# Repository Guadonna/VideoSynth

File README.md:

# VideoSynth

**R1: схемы и две разведённые PCB KiCad 9, визуальный эмулятор и результаты проверок.** Один монохромный выход 480i, шесть осцилляторов, экранная матрица до 36 связей, два CV DC…100 Гц, Eurorack 42 HP, модуль ESP32-P4.

- [Начать с обзора R1](docs/r1/README.md)
- [Скачать автономный эмулятор HTML](https://raw.githubusercontent.com/Guadonna/VideoSynth/main/dist/VideoSynth-R1.html) — сохраните файл и откройте в браузере
- [Основная схема PDF](hardware/kicad/core/core-schematic.pdf) / [схема панели PDF](hardware/kicad/panel/panel-schematic.pdf)
- [Проекты KiCad и PCB](hardware/kicad/) / [полный архив R1](dist/VideoSynth-R1-prototype.zip)
- [Проверки и ограничения](docs/r1/validation.md)
- [BOM](hardware/bom-r1.csv) / [смета](hardware/cost-estimate-usd.csv) / [испытания прототипа](docs/r1/bringup.md)

## Запуск приложения

Нужен Node.js 20+. Готовый WASM включён в репозиторий; для самого приложения установка пакетов не нужна.

```sh
npm start
```

Сервер слушает порт 4173; приложение находится по пути `/app/index.html`. В облачной среде используйте предпросмотр порта 4173. Можно также открыть скачанный `dist/VideoSynth-R1.html` без сервера: код, изображения плат и WASM встроены в файл.

**Эмулятор 0.6.2:** микс перемножает выбранные биполярные OSC; AM работает как кольцевая модуляция со сменой полярности. Для сравнения добавлены сцены «Перемножение» и «AM · инверсия». Скачайте обновлённый HTML вместо старого файла; версия указана внизу страницы. [Формулы и поведение обратной связи](docs/r1/dsp.md), [изменения и проверки](docs/r1/modulation-fixes.md).

Исправление пустого экрана из 0.6.1 сохранено: при отказе Worker автоматически включается совместимый режим с тем же WASM. [Подробности запуска](docs/r1/emulator-fixes.md).

Для тестов нужны C-компилятор и зависимости разработки:

```sh
npm ci
npm test
npm run test:browser
npm run test:spice
```

Браузерный тест запускается при работающем сервере; ему нужен Chromium (`CHROMIUM=/путь/к/chromium`). SPICE использует `libngspice`. [Полное воспроизведение сборки и CAD-проверок](docs/r1/validation.md).

R1 — инженерный прототип. Нулевые ERC/DRC и программная эмуляция не подтверждают реальный видеосигнал, устойчивость CV и скорость ESP32-P4. Готовой прошивки платы пока нет. Изготовление не заказывалось.

## История исследования

Документы прежних этапов сохранены без изменения исторических выводов:

- [ТЗ v0.4](docs/requirements/video_synth_TZ_v0.4.md), [исследование v0.4](docs/feasibility-v0.4.md)
- [ТЗ v0.5](docs/requirements/video_synth_TZ_v0.5.md), [исследование v0.5](docs/feasibility-v0.5.md), [выжимка](docs/summary-v0.5.md)

Новый запрос пользователя разрешил схему и PCB, готовый модуль ESP32-P4 и 42 HP. Численные правила модуляции R1 описаны отдельно как инженерные допущения, а не как ранее согласованные требования.

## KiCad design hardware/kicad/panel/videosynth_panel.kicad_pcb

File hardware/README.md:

# VideoSynth R1 hardware

Open `kicad/core/videosynth_core.kicad_pro` and `kicad/panel/videosynth_panel.kicad_pro` in KiCad 9. Both projects include editable schematics, routed four-layer PCBs and local symbol libraries. PDFs are `core-schematic.pdf` and `panel-schematic.pdf` in the respective folders. The two boards use separate reference-designator namespaces.

`design.json` / `tools/design.py` describe electrical connectivity and initial placement. `bom-r1.csv` lists physical parts; blank MPNs and candidates still require procurement qualification. `external-assemblies.csv` includes module, display and harnesses beyond the PCB BOM. Front-panel drawing in `panel/` is provisional.

Verification: `bash scripts/verify-hardware.sh` from the repository root. It exports schematics/netlists, runs ERC/DRC, compares all PCB pads to the manifest and runs linear CV SPICE. It does not regenerate the PCB.

**Do not run `tools/build_kicad.py` without `--schematics-only` on the finished layout: full regeneration intentionally replaces routed boards.** Router helper scripts are development tools, not a production automation pipeline.

R1 is a testable prototype design, not a manufacturing release. Mandatory module FET2 removal, power harness wiring, unqualified component substitutions, analog/timing risks and mechanical gaps are documented in [hardware.md](../docs/r1/hardware.md). No production order has been placed.

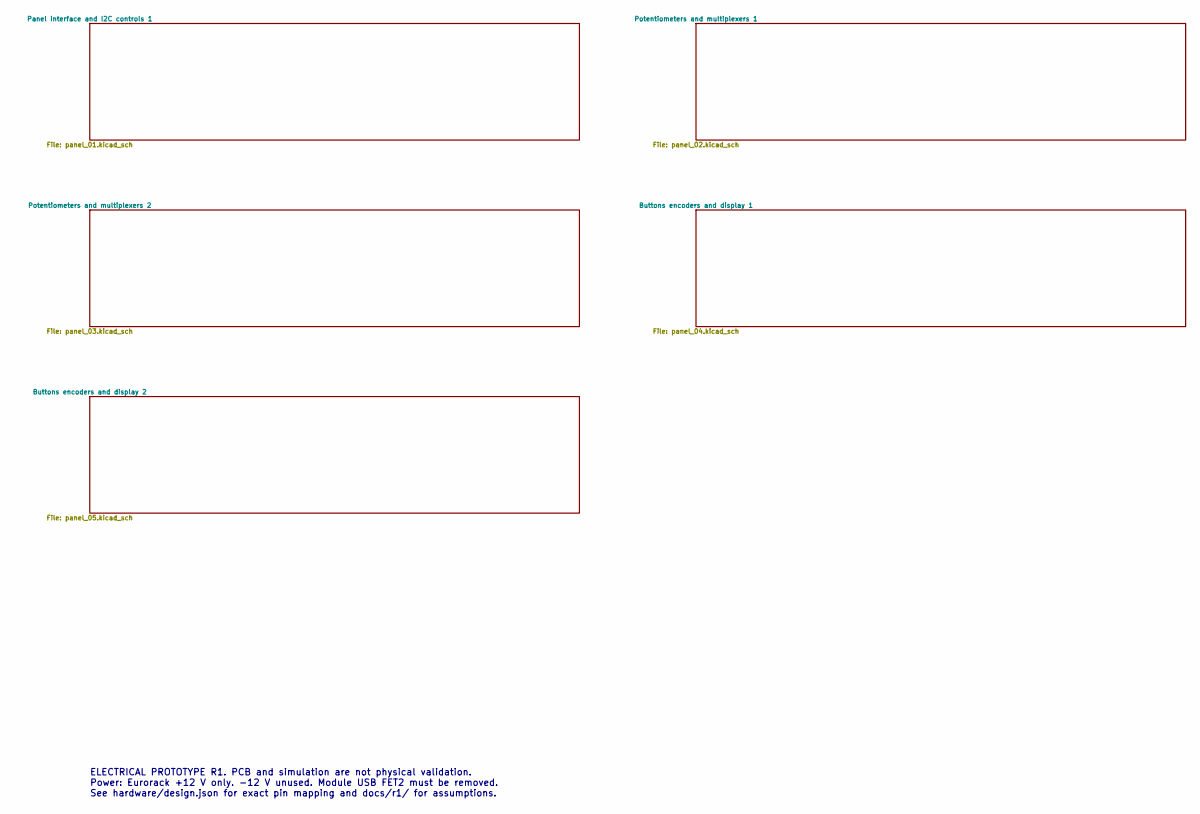
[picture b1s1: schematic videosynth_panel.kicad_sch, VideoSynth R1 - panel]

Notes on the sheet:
ELECTRICAL PROTOTYPE R1. PCB and simulation are not physical validation. Power: Eurorack +12 V only. -12 V unused. Module USB FET2 must be removed. See hardware/design.json for exact pin mapping and docs/r1/ for assumptions.

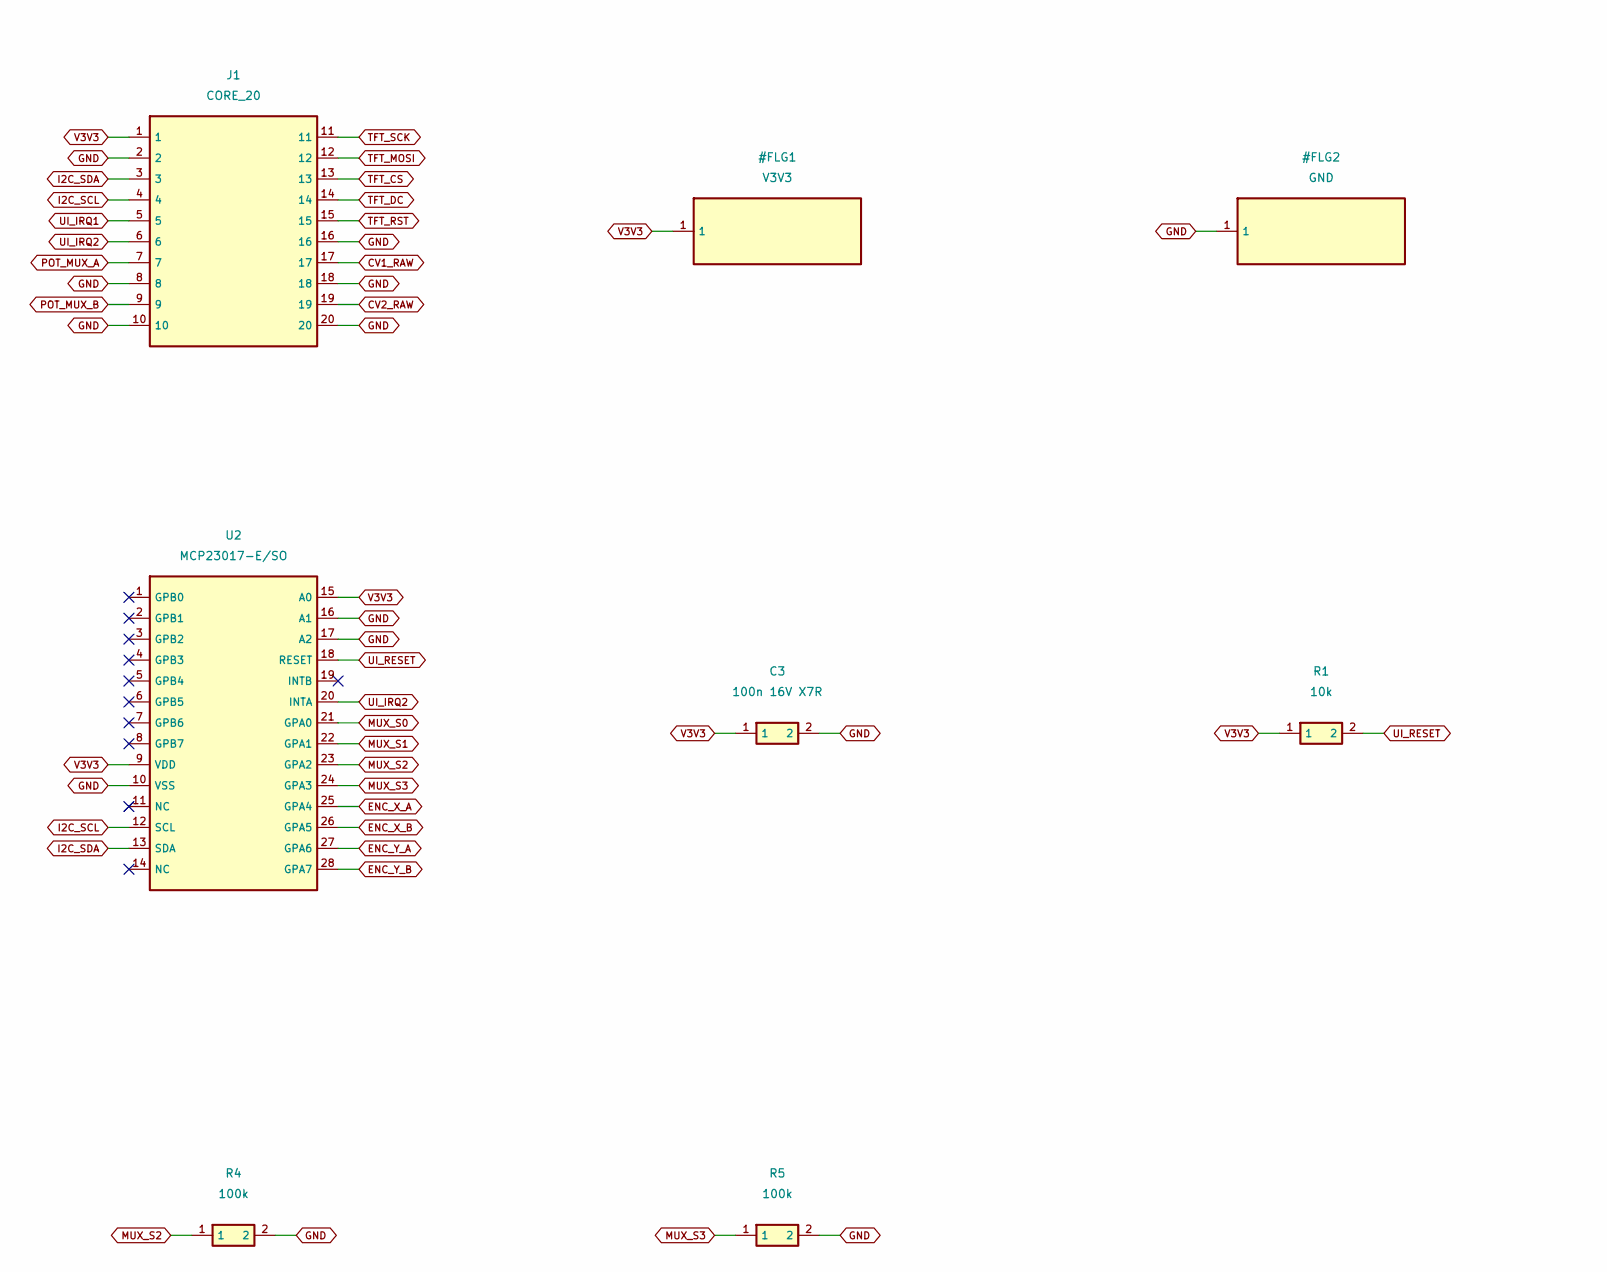
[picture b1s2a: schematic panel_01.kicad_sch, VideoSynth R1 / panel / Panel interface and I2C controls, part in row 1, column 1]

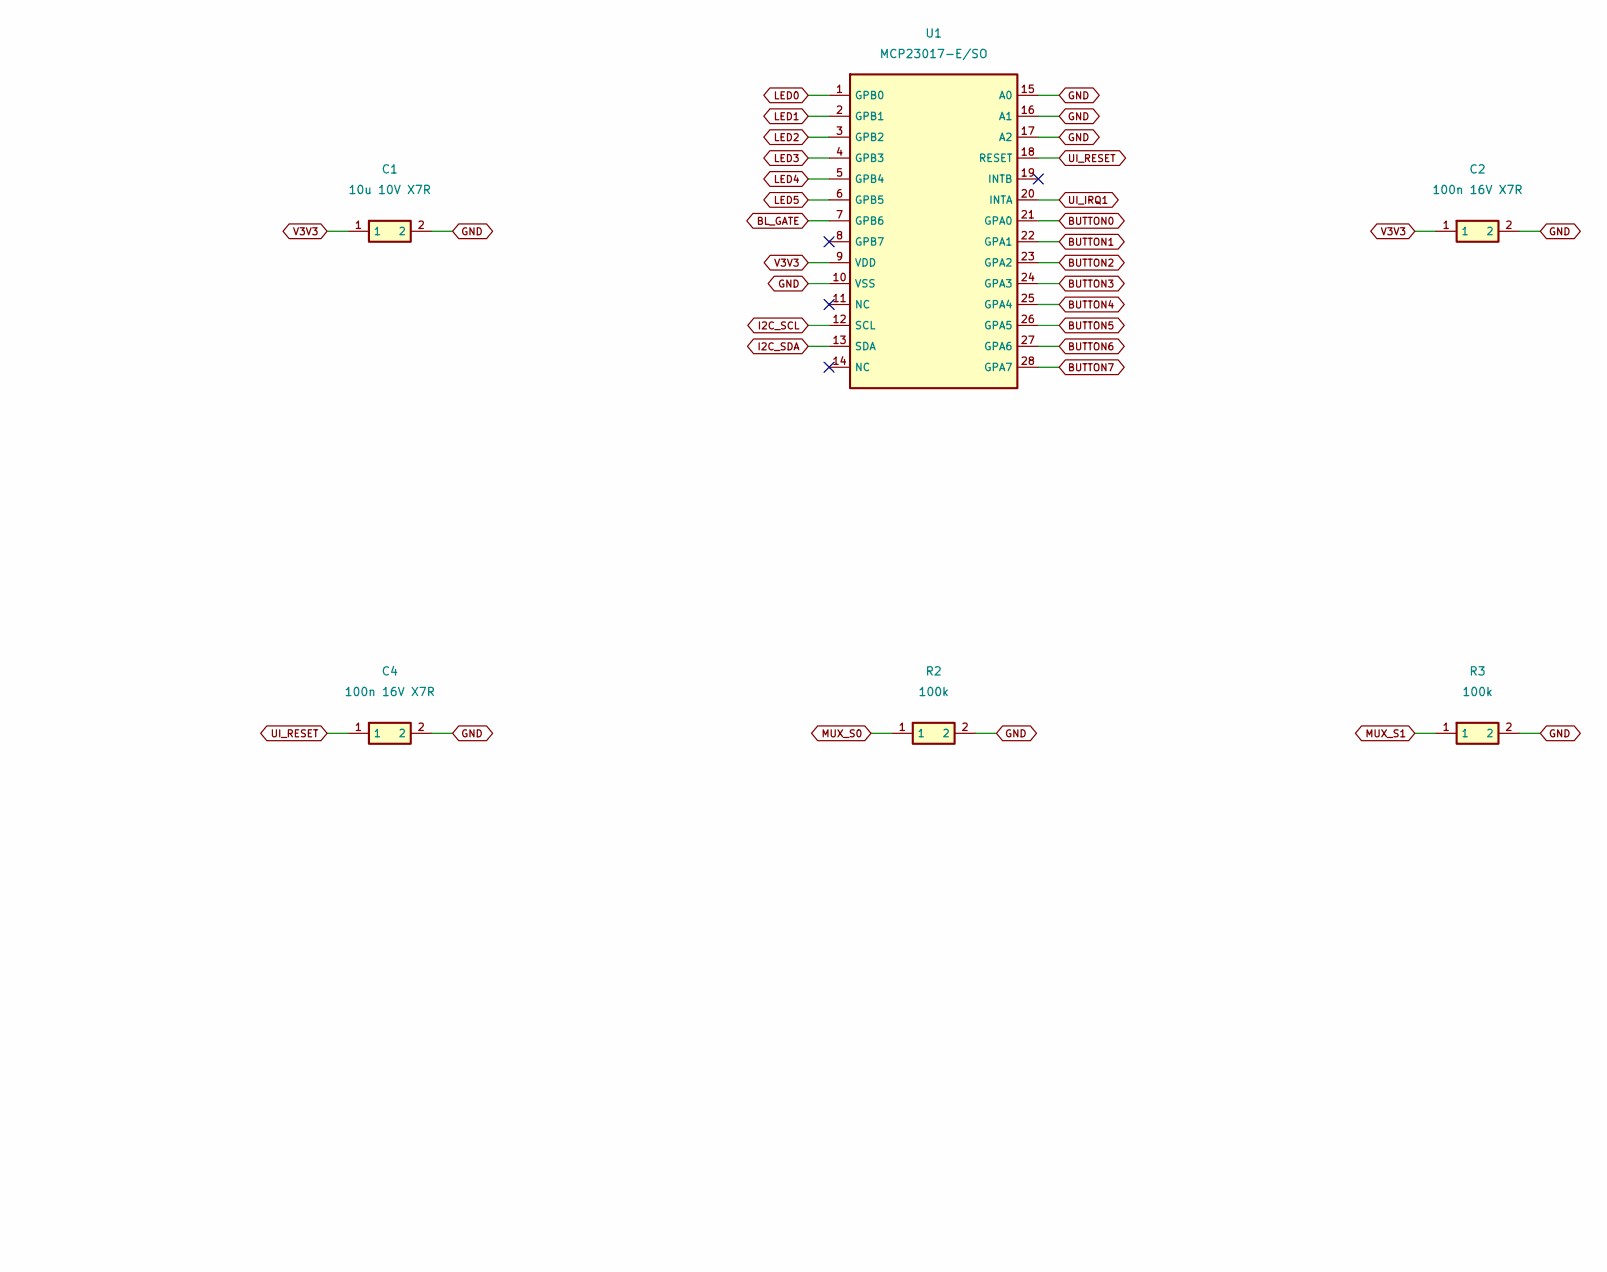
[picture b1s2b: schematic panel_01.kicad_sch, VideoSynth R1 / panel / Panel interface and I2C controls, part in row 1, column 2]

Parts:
C1: 10u 10V X7R; C_0805_2012Metric
C2, C3, C4: 100n 16V X7R; C_0805_2012Metric
J1: CORE_20; IDC-Header_2x10_P2.54mm_Vertical
R1: 10k; R_0805_2012Metric
R2, R3, R4, R5: 100k; R_0805_2012Metric
U1, U2: MCP23017-E/SO; SOIC-28W_7.5x17.9mm_P1.27mm

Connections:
BL_GATE: U1.7 (GPB6); also elsewhere on the board
BUTTON0: U1.21 (GPA0); also elsewhere on the board
BUTTON1: U1.22 (GPA1); also elsewhere on the board
BUTTON2: U1.23 (GPA2); also elsewhere on the board
BUTTON3: U1.24 (GPA3); also elsewhere on the board
BUTTON4: U1.25 (GPA4); also elsewhere on the board
BUTTON5: U1.26 (GPA5); also elsewhere on the board
BUTTON6: U1.27 (GPA6); also elsewhere on the board
BUTTON7: U1.28 (GPA7); also elsewhere on the board
CV1_RAW: J1.17; also elsewhere on the board
CV2_RAW: J1.19; also elsewhere on the board
ENC_X_A: U2.25 (GPA4); also elsewhere on the board
ENC_X_B: U2.26 (GPA5); also elsewhere on the board
ENC_Y_A: U2.27 (GPA6); also elsewhere on the board
ENC_Y_B: U2.28 (GPA7); also elsewhere on the board
GND: C1.2, C2.2, C3.2, C4.2, J1.2, J1.8, J1.10, J1.16, J1.18, J1.20, R2.2, R3.2, R4.2, R5.2, U1.10 (VSS), U1.15 (A0), U1.16 (A1), U1.17 (A2), U2.10 (VSS), U2.16 (A1), U2.17 (A2); also elsewhere on the board
I2C_SCL: J1.4, U1.12 (SCL), U2.12 (SCL)
I2C_SDA: J1.3, U1.13 (SDA), U2.13 (SDA)
LED0: U1.1 (GPB0); also elsewhere on the board
LED1: U1.2 (GPB1); also elsewhere on the board
LED2: U1.3 (GPB2); also elsewhere on the board
LED3: U1.4 (GPB3); also elsewhere on the board
LED4: U1.5 (GPB4); also elsewhere on the board
LED5: U1.6 (GPB5); also elsewhere on the board
MUX_S0: R2.1, U2.21 (GPA0); also elsewhere on the board
MUX_S1: R3.1, U2.22 (GPA1); also elsewhere on the board
MUX_S2: R4.1, U2.23 (GPA2); also elsewhere on the board
MUX_S3: R5.1, U2.24 (GPA3); also elsewhere on the board
POT_MUX_A: J1.7; also elsewhere on the board
POT_MUX_B: J1.9; also elsewhere on the board
TFT_CS: J1.13; also elsewhere on the board
TFT_DC: J1.14; also elsewhere on the board
TFT_MOSI: J1.12; also elsewhere on the board
TFT_RST: J1.15; also elsewhere on the board
TFT_SCK: J1.11; also elsewhere on the board
UI_IRQ1: J1.5, U1.20 (INTA)
UI_IRQ2: J1.6, U2.20 (INTA)
UI_RESET: C4.1, R1.2, U1.18 (RESET), U2.18 (RESET)
V3V3: C1.1, C2.1, C3.1, J1.1, R1.1, U1.9 (VDD), U2.9 (VDD), U2.15 (A0); also elsewhere on the board

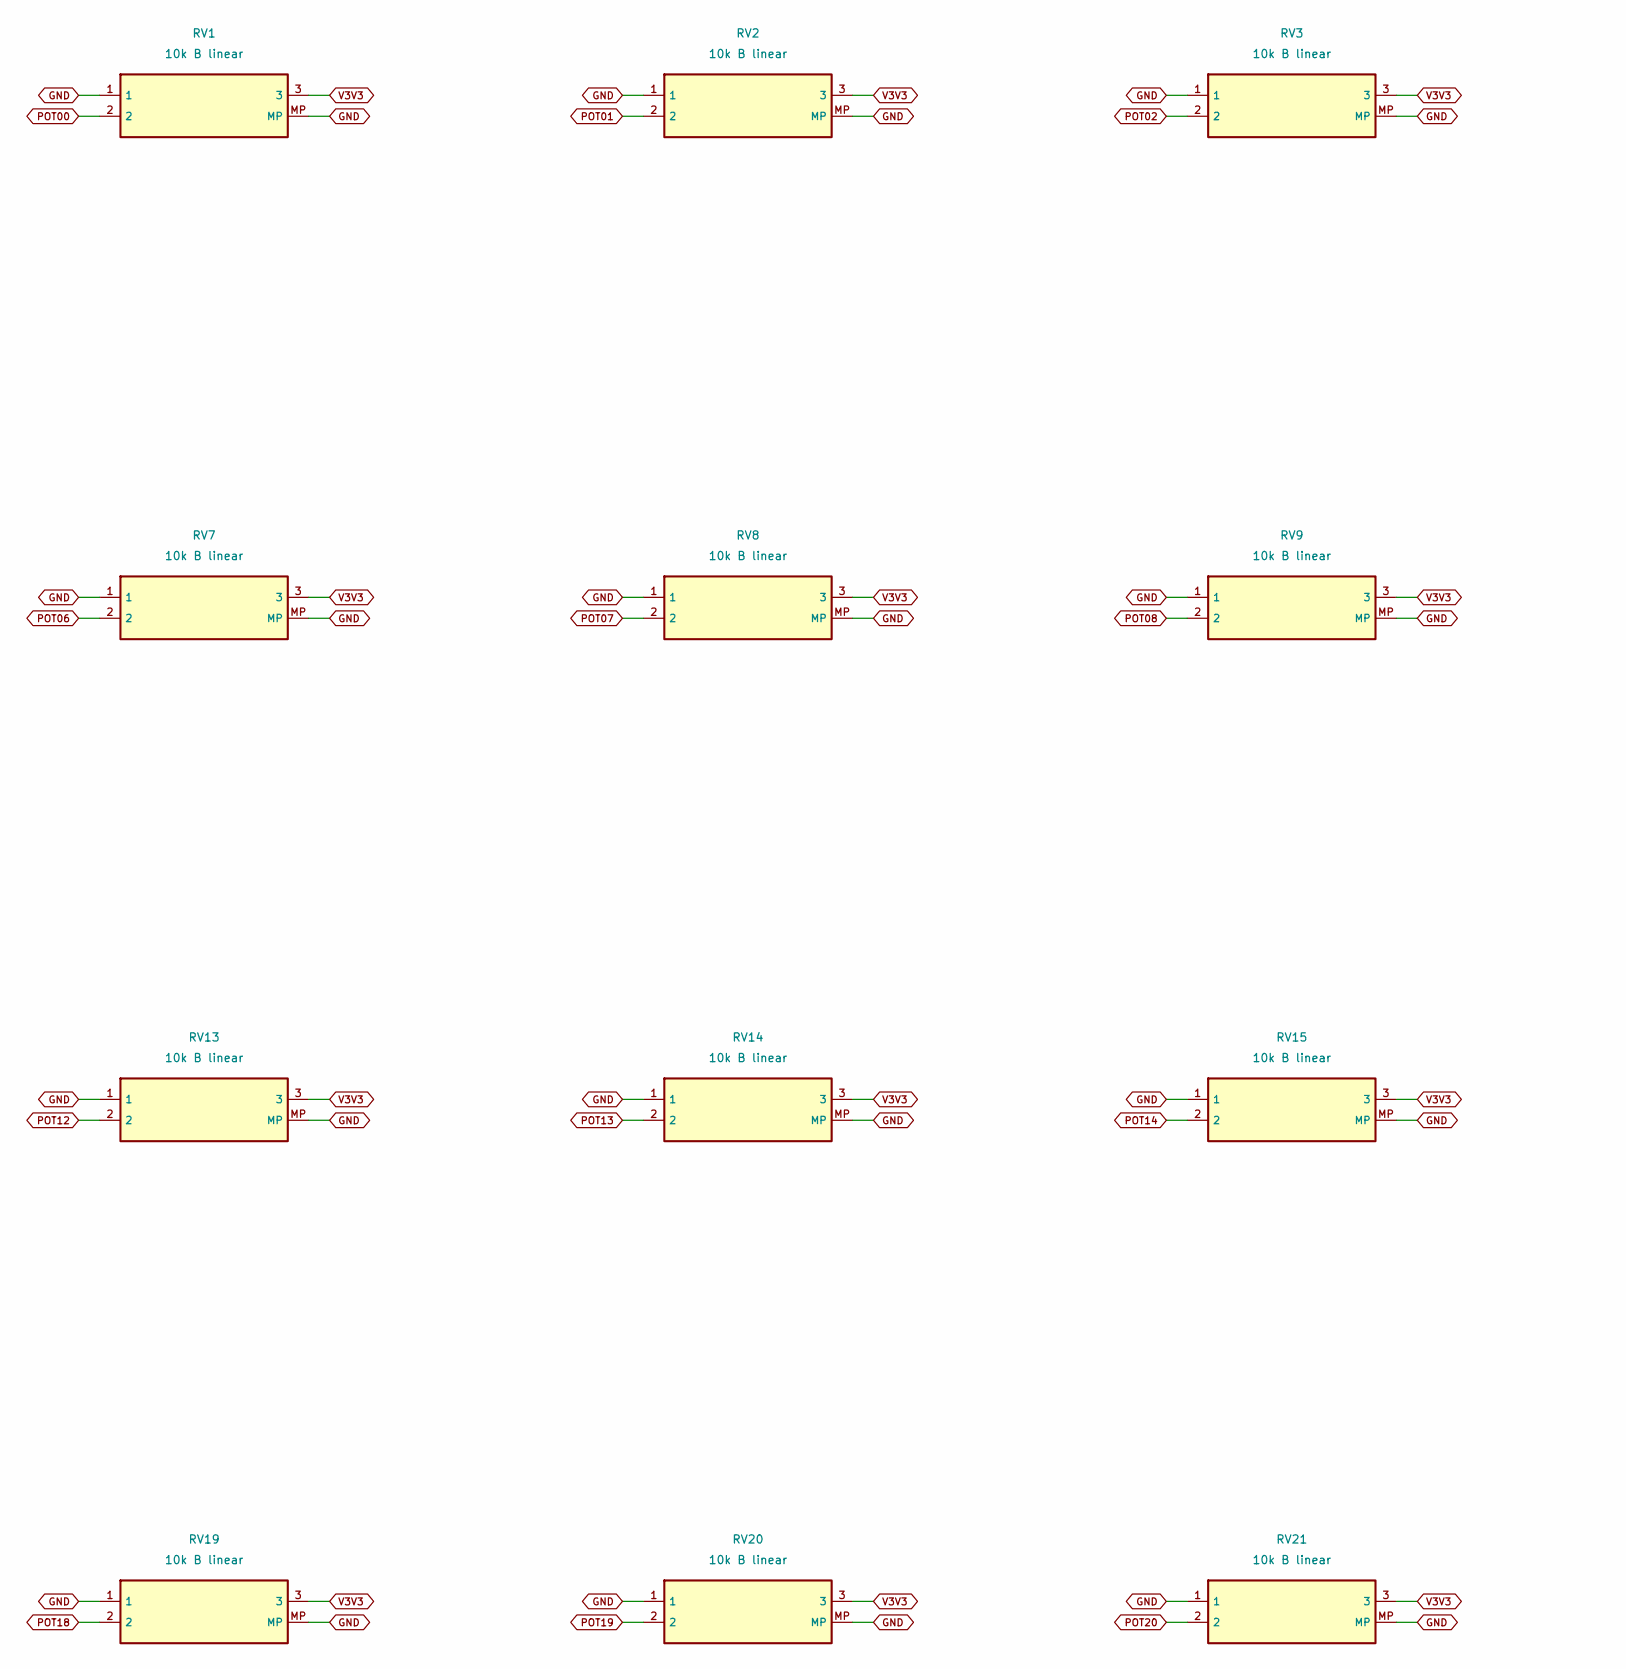
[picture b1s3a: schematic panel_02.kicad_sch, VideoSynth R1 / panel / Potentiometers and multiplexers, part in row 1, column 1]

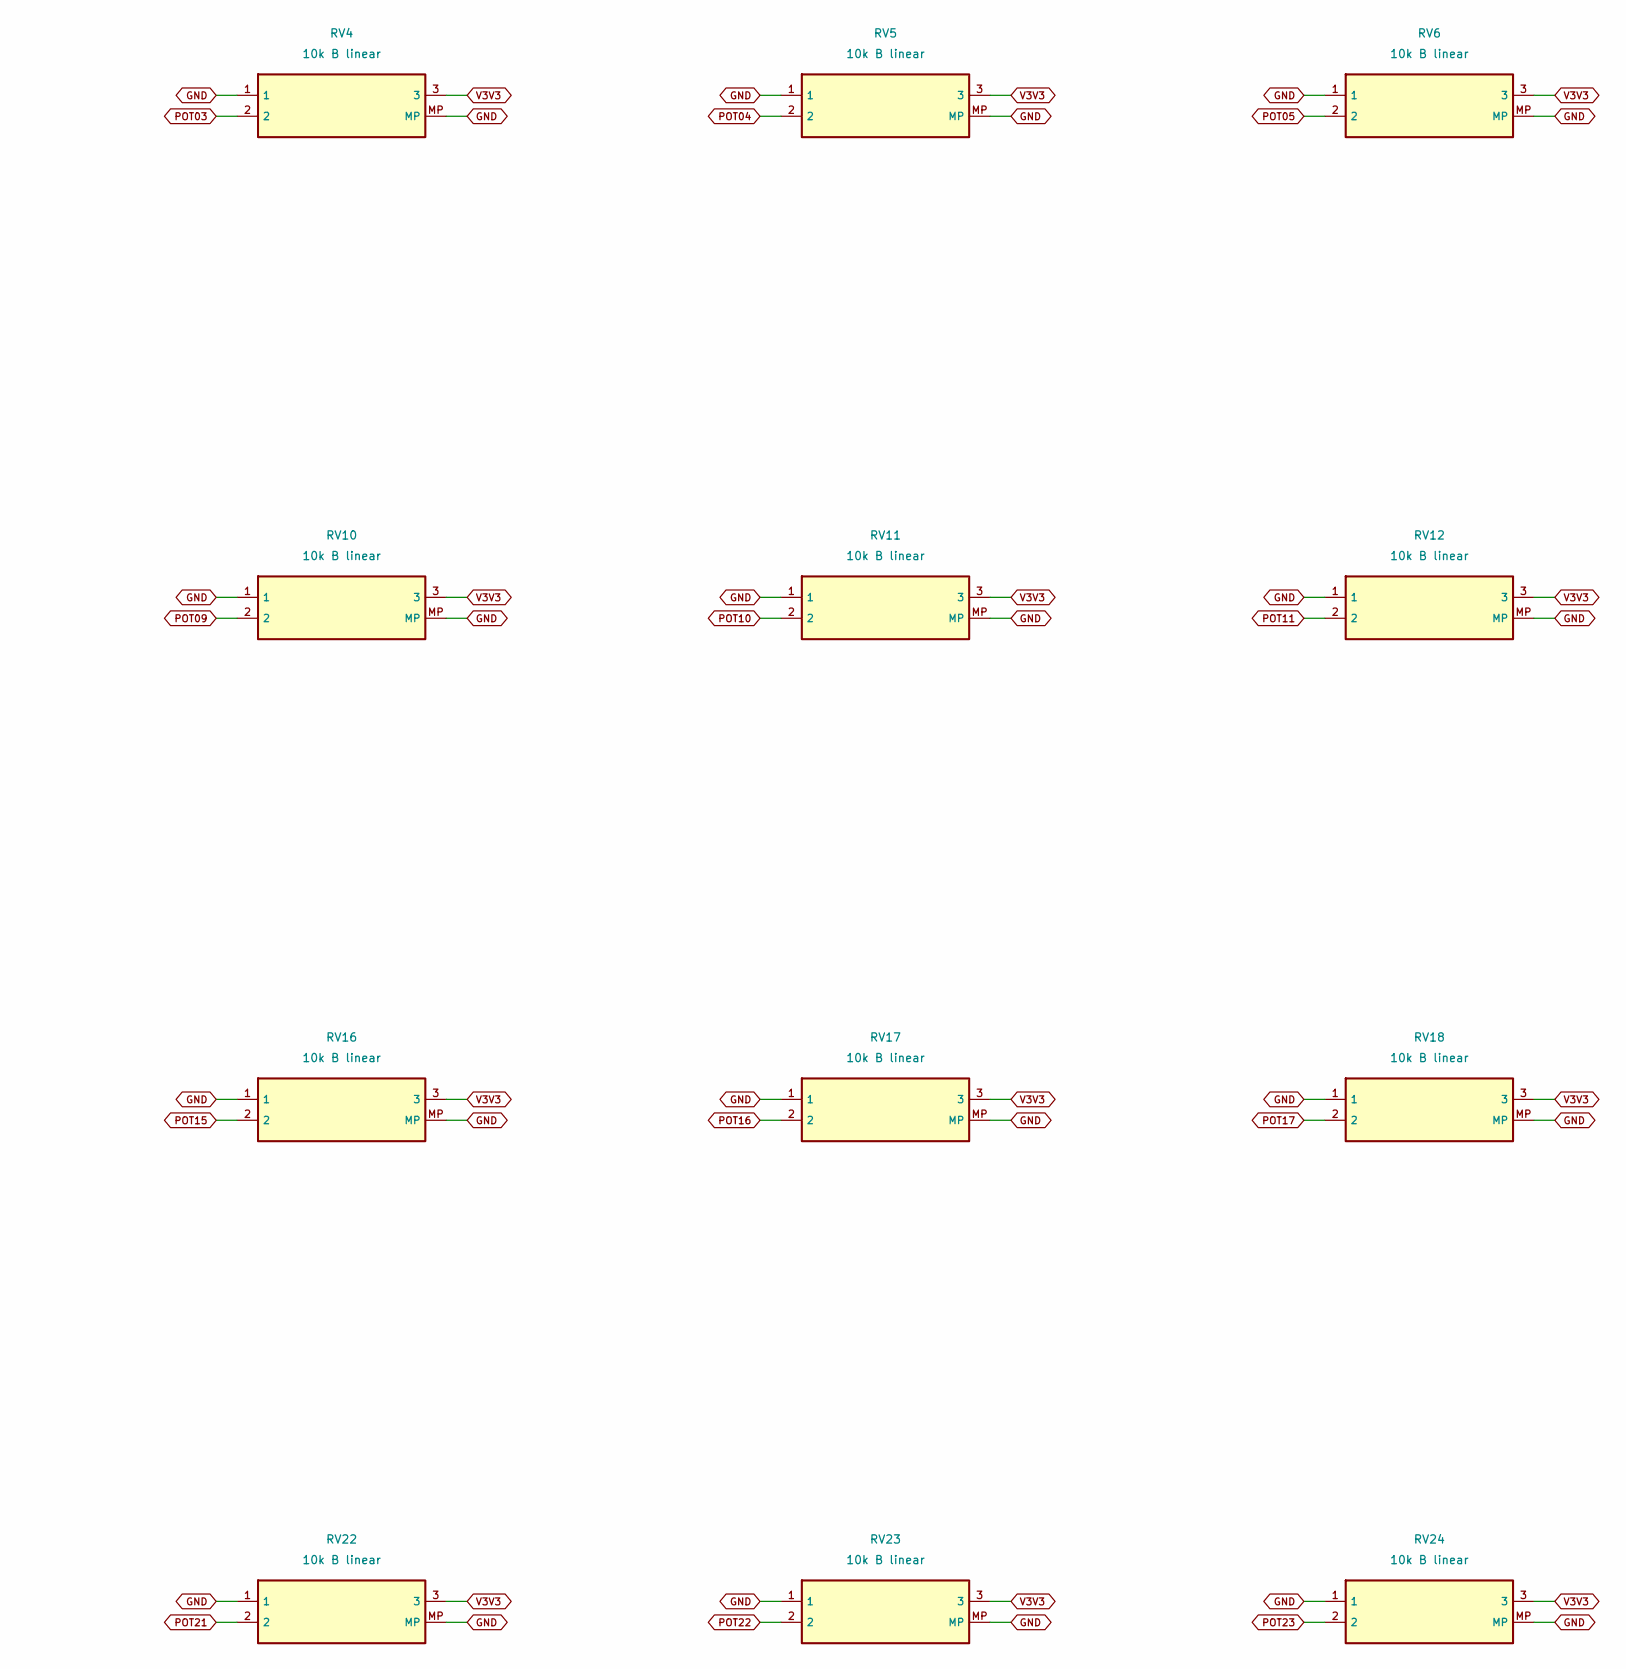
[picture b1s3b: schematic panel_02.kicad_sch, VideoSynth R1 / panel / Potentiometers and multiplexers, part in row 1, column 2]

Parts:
RV1, RV2, RV3, RV4, RV5, RV6, RV7, RV8, RV9, RV10, RV11, RV12, RV13, RV14, RV15, RV16, RV17, RV18, RV19, RV20, RV21, RV22, RV23, RV24: 10k B linear; Potentiometer_Alps_RK09K_Single_Vertical

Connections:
GND: RV1.1, RV1.MP, RV2.1, RV2.MP, RV3.1, RV3.MP, RV4.1, RV4.MP, RV5.1, RV5.MP, RV6.1, RV6.MP, RV7.1, RV7.MP, RV8.1, RV8.MP, RV9.1, RV9.MP, RV10.1, RV10.MP, RV11.1, RV11.MP, RV12.1, RV12.MP, RV13.1, RV13.MP, RV14.1, RV14.MP, RV15.1, RV15.MP, RV16.1, RV16.MP, RV17.1, RV17.MP, RV18.1, RV18.MP, RV19.1, RV19.MP, RV20.1, RV20.MP, RV21.1, RV21.MP, RV22.1, RV22.MP, RV23.1, RV23.MP, RV24.1, RV24.MP; also elsewhere on the board
POT00: RV1.2; also elsewhere on the board
POT01: RV2.2; also elsewhere on the board
POT02: RV3.2; also elsewhere on the board
POT03: RV4.2; also elsewhere on the board
POT04: RV5.2; also elsewhere on the board
POT05: RV6.2; also elsewhere on the board
POT06: RV7.2; also elsewhere on the board
POT07: RV8.2; also elsewhere on the board
POT08: RV9.2; also elsewhere on the board
POT09: RV10.2; also elsewhere on the board
POT10: RV11.2; also elsewhere on the board
POT11: RV12.2; also elsewhere on the board
POT12: RV13.2; also elsewhere on the board
POT13: RV14.2; also elsewhere on the board
POT14: RV15.2; also elsewhere on the board
POT15: RV16.2; also elsewhere on the board
POT16: RV17.2; also elsewhere on the board
POT17: RV18.2; also elsewhere on the board
POT18: RV19.2; also elsewhere on the board
POT19: RV20.2; also elsewhere on the board
POT20: RV21.2; also elsewhere on the board
POT21: RV22.2; also elsewhere on the board
POT22: RV23.2; also elsewhere on the board
POT23: RV24.2; also elsewhere on the board
V3V3: RV1.3, RV2.3, RV3.3, RV4.3, RV5.3, RV6.3, RV7.3, RV8.3, RV9.3, RV10.3, RV11.3, RV12.3, RV13.3, RV14.3, RV15.3, RV16.3, RV17.3, RV18.3, RV19.3, RV20.3, RV21.3, RV22.3, RV23.3, RV24.3; also elsewhere on the board

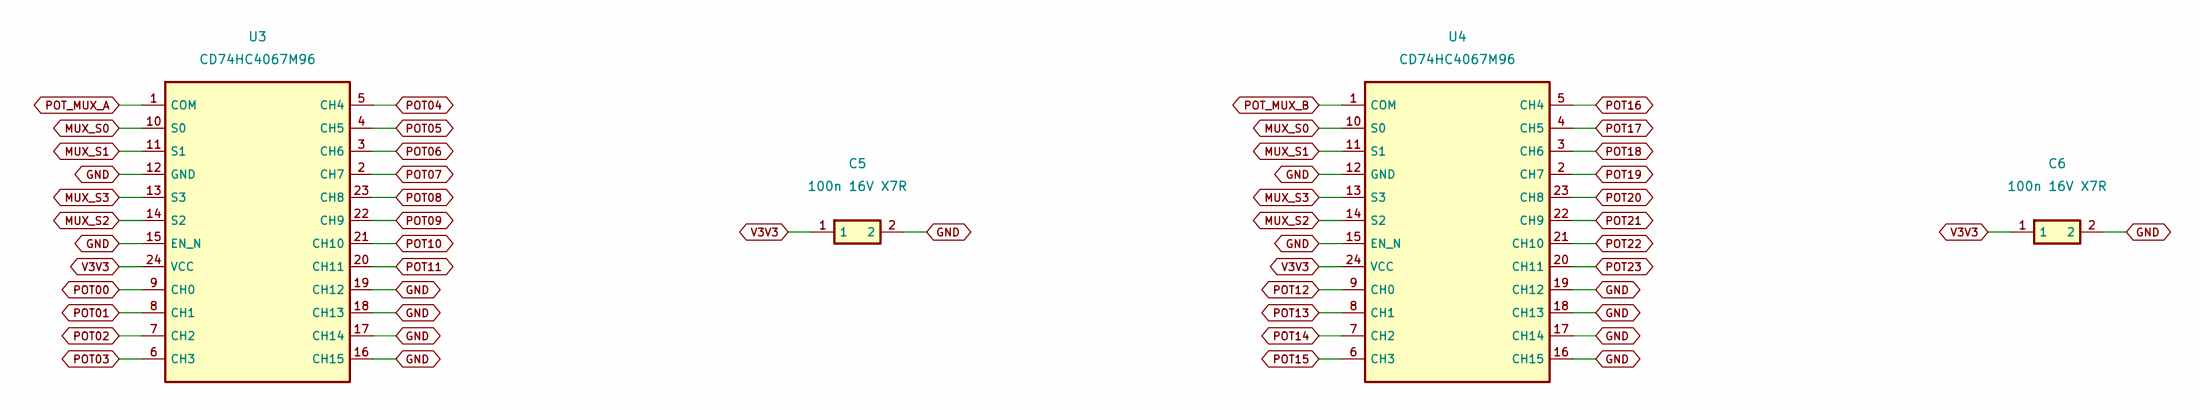
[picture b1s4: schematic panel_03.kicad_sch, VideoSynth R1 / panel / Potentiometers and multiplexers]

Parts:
C5, C6: 100n 16V X7R; C_0805_2012Metric
U3, U4: CD74HC4067M96; SOIC-24W_7.5x15.4mm_P1.27mm

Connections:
GND: C5.2, C6.2, U3.12 (GND), U3.15 (EN_N), U3.16 (CH15), U3.17 (CH14), U3.18 (CH13), U3.19 (CH12), U4.12 (GND), U4.15 (EN_N), U4.16 (CH15), U4.17 (CH14), U4.18 (CH13), U4.19 (CH12); also elsewhere on the board
MUX_S0: U3.10 (S0), U4.10 (S0); also elsewhere on the board
MUX_S1: U3.11 (S1), U4.11 (S1); also elsewhere on the board
MUX_S2: U3.14 (S2), U4.14 (S2); also elsewhere on the board
MUX_S3: U3.13 (S3), U4.13 (S3); also elsewhere on the board
POT00: U3.9 (CH0); also elsewhere on the board
POT01: U3.8 (CH1); also elsewhere on the board
POT02: U3.7 (CH2); also elsewhere on the board
POT03: U3.6 (CH3); also elsewhere on the board
POT04: U3.5 (CH4); also elsewhere on the board
POT05: U3.4 (CH5); also elsewhere on the board
POT06: U3.3 (CH6); also elsewhere on the board
POT07: U3.2 (CH7); also elsewhere on the board
POT08: U3.23 (CH8); also elsewhere on the board
POT09: U3.22 (CH9); also elsewhere on the board
POT10: U3.21 (CH10); also elsewhere on the board
POT11: U3.20 (CH11); also elsewhere on the board
POT12: U4.9 (CH0); also elsewhere on the board
POT13: U4.8 (CH1); also elsewhere on the board
POT14: U4.7 (CH2); also elsewhere on the board
POT15: U4.6 (CH3); also elsewhere on the board
POT16: U4.5 (CH4); also elsewhere on the board
POT17: U4.4 (CH5); also elsewhere on the board
POT18: U4.3 (CH6); also elsewhere on the board
POT19: U4.2 (CH7); also elsewhere on the board
POT20: U4.23 (CH8); also elsewhere on the board
POT21: U4.22 (CH9); also elsewhere on the board
POT22: U4.21 (CH10); also elsewhere on the board
POT23: U4.20 (CH11); also elsewhere on the board
POT_MUX_A: U3.1 (COM); also elsewhere on the board
POT_MUX_B: U4.1 (COM); also elsewhere on the board
V3V3: C5.1, C6.1, U3.24 (VCC), U4.24 (VCC); also elsewhere on the board

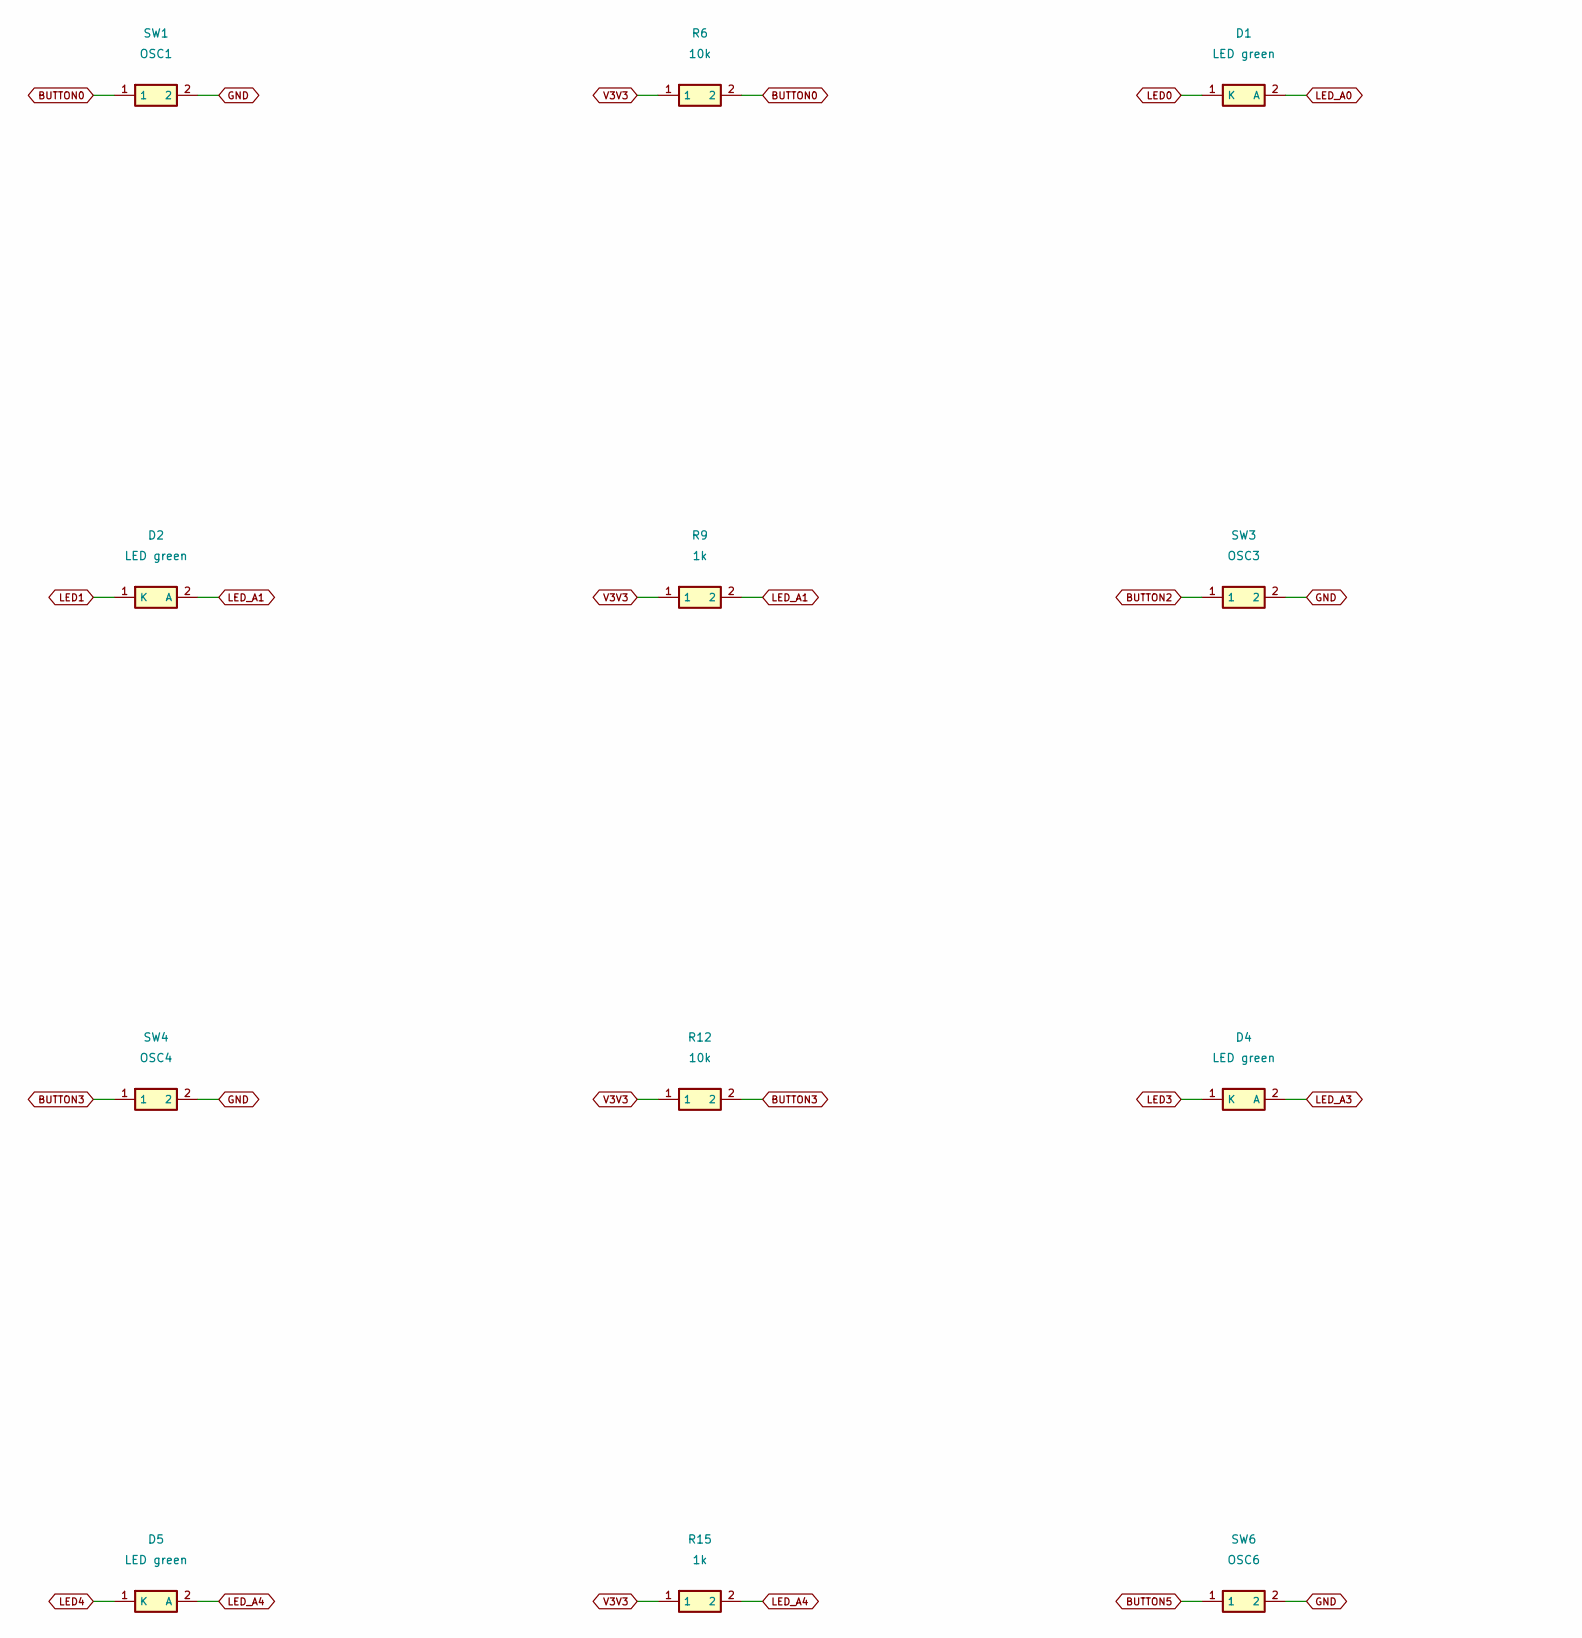
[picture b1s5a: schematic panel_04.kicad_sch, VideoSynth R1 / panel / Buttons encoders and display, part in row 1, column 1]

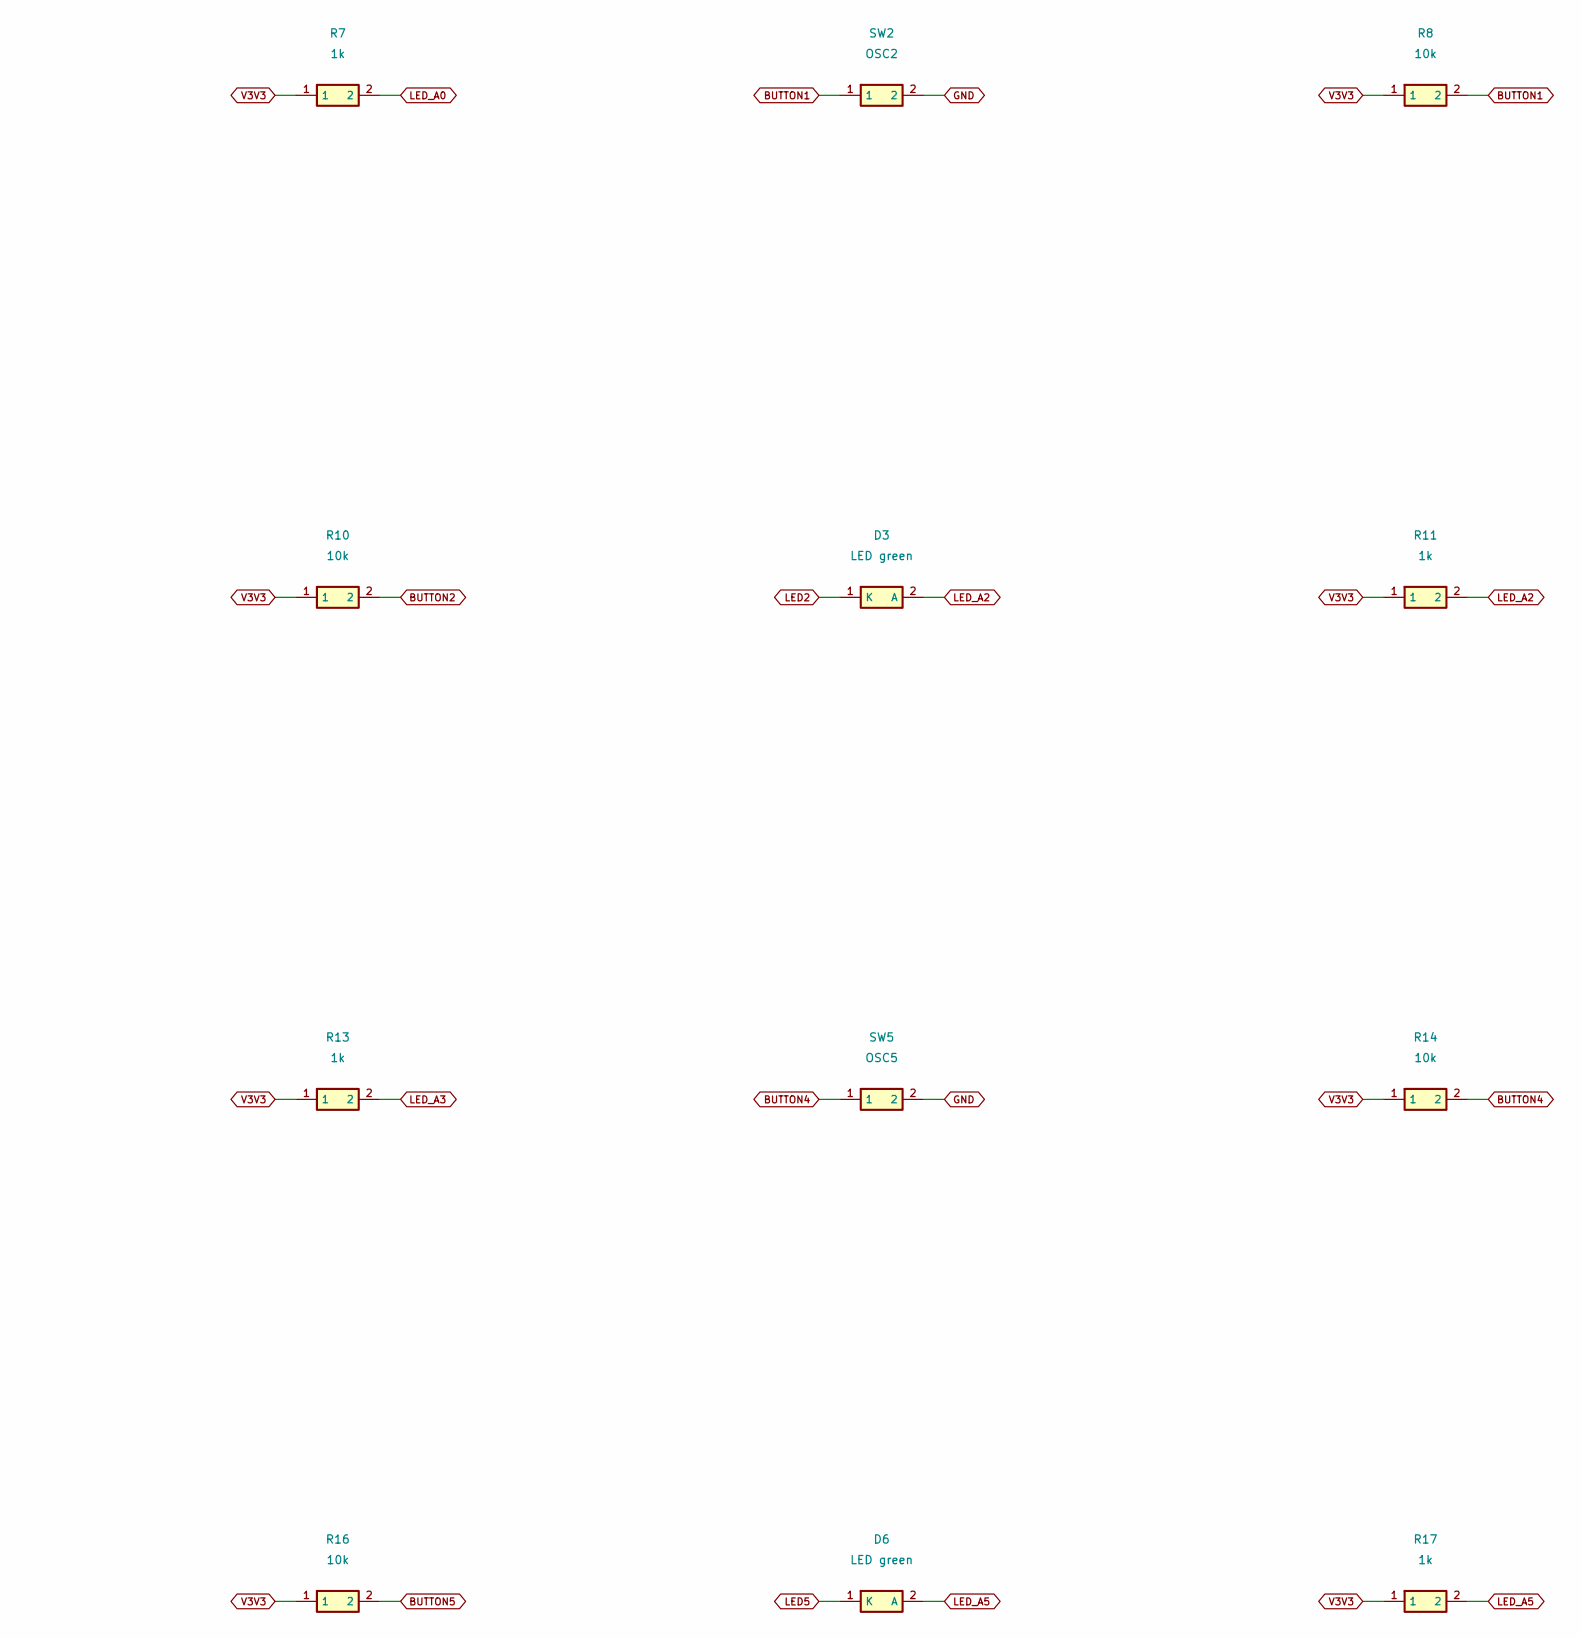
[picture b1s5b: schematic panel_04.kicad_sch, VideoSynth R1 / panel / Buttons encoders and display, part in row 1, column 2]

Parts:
D1, D2, D3, D4, D5, D6: LED green; LED_0603_1608Metric
R6, R8, R10, R12, R14, R16: 10k; R_0805_2012Metric
R7, R9, R11, R13, R15, R17: 1k; R_0805_2012Metric
SW1: OSC1; SW_PUSH_6mm
SW2: OSC2; SW_PUSH_6mm
SW3: OSC3; SW_PUSH_6mm
SW4: OSC4; SW_PUSH_6mm
SW5: OSC5; SW_PUSH_6mm
SW6: OSC6; SW_PUSH_6mm

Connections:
BUTTON0: R6.2, SW1.1; also elsewhere on the board
BUTTON1: R8.2, SW2.1; also elsewhere on the board
BUTTON2: R10.2, SW3.1; also elsewhere on the board
BUTTON3: R12.2, SW4.1; also elsewhere on the board
BUTTON4: R14.2, SW5.1; also elsewhere on the board
BUTTON5: R16.2, SW6.1; also elsewhere on the board
GND: SW1.2, SW2.2, SW3.2, SW4.2, SW5.2, SW6.2; also elsewhere on the board
LED0: D1.1 (K); also elsewhere on the board
LED1: D2.1 (K); also elsewhere on the board
LED2: D3.1 (K); also elsewhere on the board
LED3: D4.1 (K); also elsewhere on the board
LED4: D5.1 (K); also elsewhere on the board
LED5: D6.1 (K); also elsewhere on the board
LED_A0: D1.2 (A), R7.2
LED_A1: D2.2 (A), R9.2
LED_A2: D3.2 (A), R11.2
LED_A3: D4.2 (A), R13.2
LED_A4: D5.2 (A), R15.2
LED_A5: D6.2 (A), R17.2
V3V3: R6.1, R7.1, R8.1, R9.1, R10.1, R11.1, R12.1, R13.1, R14.1, R15.1, R16.1, R17.1; also elsewhere on the board
